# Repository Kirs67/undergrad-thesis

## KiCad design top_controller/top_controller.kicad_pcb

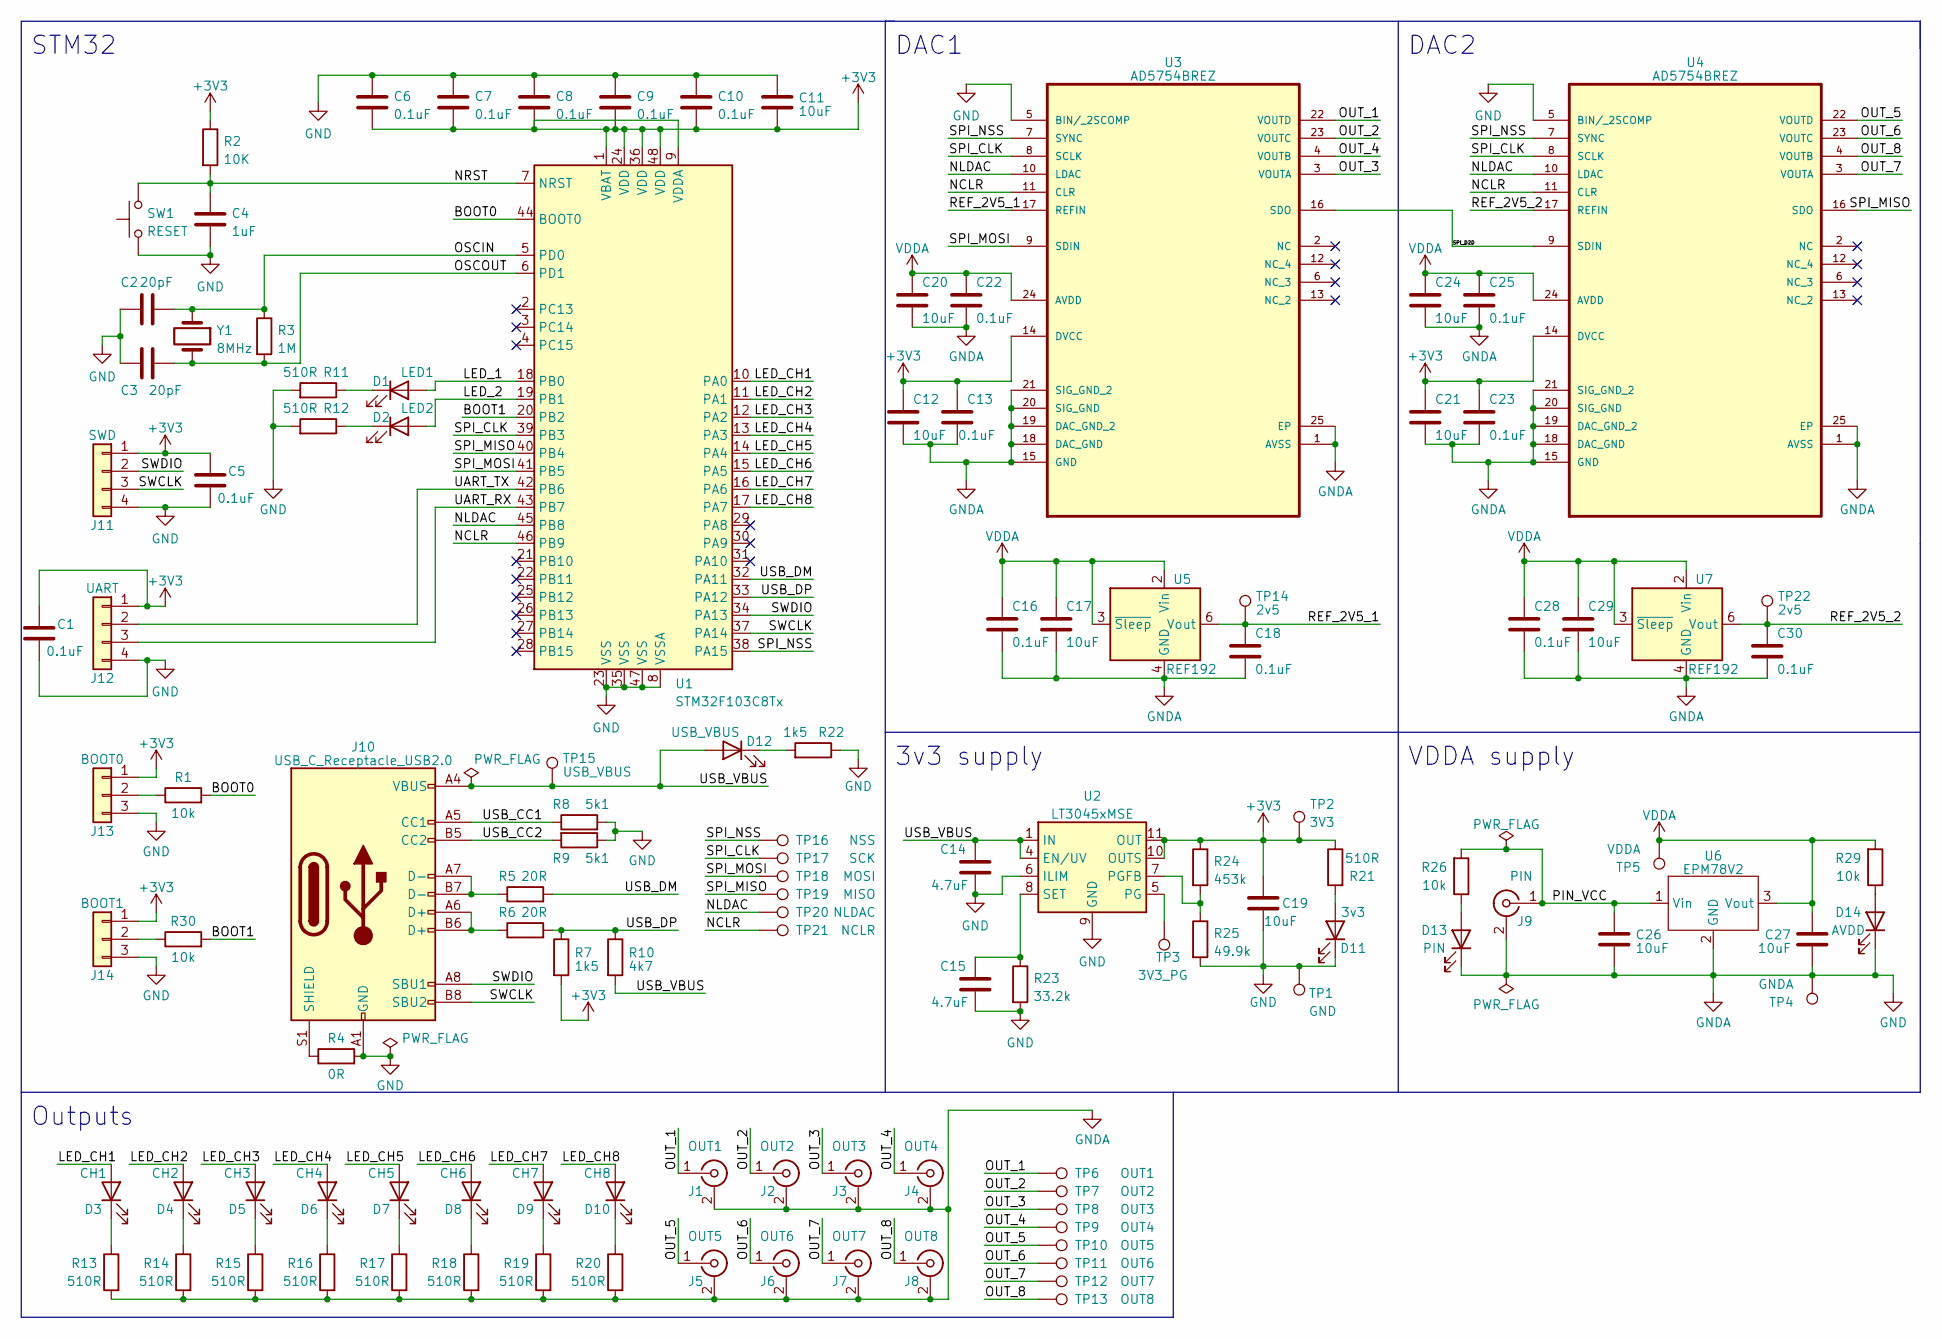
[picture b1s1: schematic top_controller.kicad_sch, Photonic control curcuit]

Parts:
C1, C5, C6, C7, C8, C9, C10, C13, C16, C18, C22, C23, C25, C28, C30: 0.1uF; C_0603_1608Metric
C2, C3: 20pF; C_0603_1608Metric
C4: 1uF; C_0603_1608Metric
C11, C12, C17, C19, C20, C21, C24, C26, C27, C29: 10uF; C_1206_3216Metric
C14, C15: 4.7uF; C_1206_3216Metric
D1: LED1; LED_0805_2012Metric
D2: LED2; LED_0805_2012Metric
D3: CH1; LED_0805_2012Metric
D4: CH2; LED_0805_2012Metric
D5: CH3; LED_0805_2012Metric
D6: CH4; LED_0805_2012Metric
D7: CH5; LED_0805_2012Metric
D8: CH6; LED_0805_2012Metric
D9: CH7; LED_0805_2012Metric
D10: CH8; LED_0805_2012Metric
D11: 3v3; LED_0805_2012Metric
D12: USB_VBUS; LED_0805_2012Metric
D13: PIN; LED_0805_2012Metric
D14: AVDD; LED_0805_2012Metric
J1: OUT1; CONBNC002
J2: OUT2; CONBNC002
J3: OUT3; CONBNC002
J4: OUT4; CONBNC002
J5: OUT5; CONBNC002
J6: OUT6; CONBNC002
J7: OUT7; CONBNC002
J8: OUT8; CONBNC002
J9: PIN; CONBNC002
J10: USB_C_Receptacle_USB2.0; USB_C_Receptacle_GCT_USB4105-xx-A_16P_TopMnt_Horizontal
J11: SWD; PinHeader_1x04_P2.54mm_Vertical
J12: UART; PinHeader_1x04_P2.54mm_Vertical
J13: BOOT0; PinHeader_1x03_P2.54mm_Vertical
J14: BOOT1; PinHeader_1x03_P2.54mm_Vertical
R1, R26, R29, R30: 10k; R_0603_1608Metric
R2: 10K; R_0603_1608Metric
R3: 1M; R_2512_6332Metric
R4: 0R; R_0603_1608Metric
R5, R6: 20R; R_0603_1608Metric
R7, R22: 1k5; R_0603_1608Metric
R8, R9: 5k1; R_0603_1608Metric
R10: 4k7; R_0603_1608Metric
R11, R12, R13, R14, R15, R16, R17, R18, R19, R20, R21: 510R; R_0603_1608Metric
R23: 33.2k; R_0603_1608Metric
R24: 453k; R_0805_2012Metric
R25: 49.9k; R_0603_1608Metric
SW1: RESET; SW_TS04-66-95-BK-100-SMT
TP1: GND; TestPoint_Keystone_5010-5014_Multipurpose
TP2: 3V3; TestPoint_Keystone_5010-5014_Multipurpose
TP3: 3V3_PG; TestPoint_Keystone_5010-5014_Multipurpose
TP4: GNDA; TestPoint_Keystone_5010-5014_Multipurpose
TP5: VDDA; TestPoint_Keystone_5010-5014_Multipurpose
TP6: OUT1; TestPoint_Keystone_5010-5014_Multipurpose
TP7: OUT2; TestPoint_Keystone_5010-5014_Multipurpose
TP8: OUT3; TestPoint_Keystone_5010-5014_Multipurpose
TP9: OUT4; TestPoint_Keystone_5010-5014_Multipurpose
TP10: OUT5; TestPoint_Keystone_5010-5014_Multipurpose
TP11: OUT6; TestPoint_Keystone_5010-5014_Multipurpose
TP12: OUT7; TestPoint_Keystone_5010-5014_Multipurpose
TP13: OUT8; TestPoint_Keystone_5010-5014_Multipurpose
TP14, TP22: 2v5; TestPoint_Keystone_5010-5014_Multipurpose
TP15: USB_VBUS; TestPoint_Keystone_5010-5014_Multipurpose
TP16: NSS; TestPoint_Keystone_5010-5014_Multipurpose
TP17: SCK; TestPoint_Keystone_5010-5014_Multipurpose
TP18: MOSI; TestPoint_Keystone_5010-5014_Multipurpose
TP19: MISO; TestPoint_Keystone_5010-5014_Multipurpose
TP20: NLDAC; TestPoint_Keystone_5010-5014_Multipurpose
TP21: NCLR; TestPoint_Keystone_5010-5014_Multipurpose
U1: STM32F103C8Tx; LQFP-48_7x7mm_P0.5mm
U2: LT3045xMSE; MSOP-12-1EP_3x4mm_P0.65mm_EP1.65x2.85mm
U3, U4: AD5754BREZ; SOP65P640X120-25N; MPN AD5754BREZ
U5, U7: REF192; SOIC-8_3.9x4.9mm_P1.27mm
U6: EPM78V2
Y1: 8MHz; Crystal_SMD_HC49-SD

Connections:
+3V3: C1.1, C5.1, C6.2, C7.2, C8.2, C9.2, C10.2, C11.2, C12.1, C13.1, C19.1, C21.1, C23.1, J11.1, J12.1, J13.1, J14.1, R2.1, R7.2, R21.1, R24.1, TP2.1, U1.1 (VBAT), U1.9 (VDDA), U1.24 (VDD), U1.36 (VDD), U1.48 (VDD), U2.10 (OUTS), U2.11 (OUT), U2.12 (OUT), U3.14 (DVCC), U4.14 (DVCC)
/BOOT0: R1.2, U1.44 (BOOT0)
/BOOT1: R30.2, U1.20 (PB2)
/LED_1: D1.2 (A), U1.18 (PB0)
/LED_2: D2.2 (A), U1.19 (PB1)
/LED_CH1: D3.2 (A), U1.10 (PA0)
/LED_CH2: D4.2 (A), U1.11 (PA1)
/LED_CH3: D5.2 (A), U1.12 (PA2)
/LED_CH4: D6.2 (A), U1.13 (PA3)
/LED_CH5: D7.2 (A), U1.14 (PA4)
/LED_CH6: D8.2 (A), U1.15 (PA5)
/LED_CH7: D9.2 (A), U1.16 (PA6)
/LED_CH8: D10.2 (A), U1.17 (PA7)
/NCLR: TP21.1, U1.46 (PB9), U3.11 (CLR), U4.11 (CLR)
/NLDAC: TP20.1, U1.45 (PB8), U3.10 (LDAC), U4.10 (LDAC)
/NRST: C4.1, R2.2, SW1.2, U1.7 (NRST)
/OSCIN: C2.1, R3.1, U1.5 (PD0), Y1.1
/OSCOUT: C3.1, R3.2, U1.6 (PD1), Y1.2
/OUT_1: J1.1 (In), TP6.1, U3.22 (VOUTD)
/OUT_2: J2.1 (In), TP7.1, U3.23 (VOUTC)
/OUT_3: J3.1 (In), TP8.1, U3.3 (VOUTA)
/OUT_4: J4.1 (In), TP9.1, U3.4 (VOUTB)
/OUT_5: J5.1 (In), TP10.1, U4.22 (VOUTD)
/OUT_6: J6.1 (In), TP11.1, U4.23 (VOUTC)
/OUT_7: J7.1 (In), TP12.1, U4.3 (VOUTA)
/OUT_8: J8.1 (In), TP13.1, U4.4 (VOUTB)
/PIN_VCC: C26.1, J9.1 (In), R26.2, U6.1 (Vin)
/REF_2V5_1: C18.1, TP14.1, U3.17 (REFIN), U5.6 (Vout)
/REF_2V5_2: C30.1, TP22.1, U4.17 (REFIN), U7.6 (Vout)
/SPI_CLK: TP17.1, U1.39 (PB3), U3.8 (SCLK), U4.8 (SCLK)
/SPI_D2D: U3.16 (SDO), U4.9 (SDIN)
/SPI_MISO: TP19.1, U1.40 (PB4), U4.16 (SDO)
/SPI_MOSI: TP18.1, U1.41 (PB5), U3.9 (SDIN)
/SPI_NSS: TP16.1, U1.38 (PA15), U3.7 (SYNC), U4.7 (SYNC)
/SWCLK: J10.B8 (SBU2), J11.3, U1.37 (PA14)
/SWDIO: J10.A8 (SBU1), J11.2, U1.34 (PA13)
/UART_RX: J12.3, U1.43 (PB7)
/UART_TX: J12.2, U1.42 (PB6)
/USB_CC1: J10.A5 (CC1), R8.1
/USB_CC2: J10.B5 (CC2), R9.2
/USB_DM: R5.2, U1.32 (PA11)
/USB_DP: R6.2, R7.1, R10.1, U1.33 (PA12)
/USB_VBUS: C14.1, D12.2 (A), J10.A4 (VBUS), J10.A9 (VBUS), J10.B4 (VBUS), J10.B9 (VBUS), R10.2, TP15.1, U2.1 (IN), U2.2 (IN), U2.3 (IN), U2.4 (EN/UV)
GND: C1.2, C2.2, C3.2, C4.2, C5.2, C6.1, C7.1, C8.1, C9.1, C10.1, C11.1, C12.2, C13.2, C14.2, C15.2, C16.2, C17.2, C18.2, C19.2, C20.2, C21.2, C22.2, C23.2, C24.2, C25.2, C26.2, C27.2, C28.2, C29.2, C30.2, D11.1 (K), D13.1 (K), D14.1 (K), J1.2 (Ext), J2.2 (Ext), J3.2 (Ext), J4.2 (Ext), J5.2 (Ext), J6.2 (Ext), J7.2 (Ext), J8.2 (Ext), J9.2 (Ext), J10.A1 (GND), J10.A12 (GND), J10.B1 (GND), J10.B12 (GND), J11.4, J12.4, J13.3, J14.3, R4.2, R8.2, R9.1, R11.2, R12.2, R13.2, R14.2, R15.2, R16.2, R17.2, R18.2, R19.2, R20.2, R22.1, R23.2, R25.2, SW1.1, TP1.1, TP4.1, U1.8 (VSSA), U1.23 (VSS), U1.35 (VSS), U1.47 (VSS), U2.6 (ILIM), U2.9 (GND), U2.13 (GND), U3.1 (AVSS), U3.5 (BIN/_2SCOMP), U3.15 (GND), U3.18 (DAC_GND), U3.19 (DAC_GND_2), U3.20 (SIG_GND), U3.21 (SIG_GND_2), U3.25 (EP), U4.1 (AVSS), U4.5 (BIN/_2SCOMP), U4.15 (GND), U4.18 (DAC_GND), U4.19 (DAC_GND_2), U4.20 (SIG_GND), U4.21 (SIG_GND_2), U4.25 (EP), U5.4 (GND), U6.2 (GND), U7.4 (GND)
unnamed: D1.1 (K), R11.1
unnamed: D2.1 (K), R12.1
unnamed: D3.1 (K), R13.1
unnamed: D4.1 (K), R14.1
unnamed: D5.1 (K), R15.1
unnamed: D6.1 (K), R16.1
unnamed: D7.1 (K), R17.1
unnamed: D8.1 (K), R18.1
unnamed: D9.1 (K), R19.1
unnamed: D10.1 (K), R20.1
unnamed: D11.2 (A), R21.2
unnamed: D12.1 (K), R22.2
unnamed: D13.2 (A), R26.1
unnamed: D14.2 (A), R29.1
unnamed: J10.A6 (D+), J10.B6 (D+), R6.1
unnamed: J10.A7 (D-), J10.B7 (D-), R5.1
unnamed: J10.S1 (SHIELD), R4.1
unnamed: J13.2, R1.1
unnamed: J14.2, R30.1
unnamed: TP3.1, U2.5 (PG)
unnamed: R24.2, R25.1, U2.7 (PGFB)
unnamed: C15.1, R23.1, U2.8 (SET)
VDDA: C16.1, C17.1, C20.1, C22.1, C24.1, C25.1, C27.1, C28.1, C29.1, R29.2, TP5.1, U3.24 (AVDD), U4.24 (AVDD), U5.2 (Vin), U5.3 (~Sleep), U6.3 (Vout), U7.2 (Vin), U7.3 (~Sleep)

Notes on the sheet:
DAC2
3v3 supply
Outputs
DAC1
VDDA supply
STM32

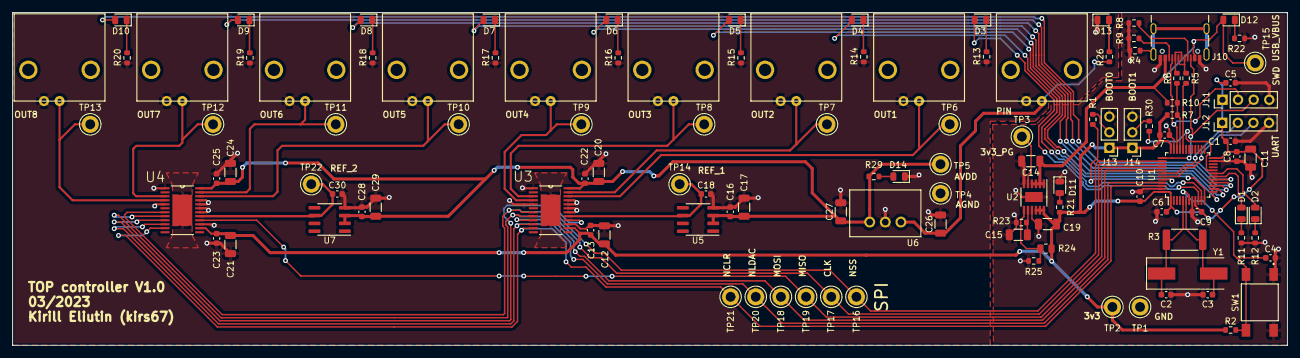
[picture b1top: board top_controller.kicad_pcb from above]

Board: 2 copper layers, 207.7 x 54.2 mm, 117 parts (0 on the bottom side), 67 nets.

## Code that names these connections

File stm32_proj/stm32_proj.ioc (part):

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Mcu.Name=STM32F103C(8-B)Tx
Mcu.Package=LQFP48
Mcu.UserName=STM32F103C8Tx
PA0-WKUP.GPIOParameters=GPIO_Label
PA0-WKUP.GPIO_Label=LED_CH1
PA0-WKUP.Signal=GPIO_Output
PA1.GPIOParameters=GPIO_Label
PA1.GPIO_Label=LED_CH2
PA1.Signal=GPIO_Output
PA11.Mode=Device
PA11.Signal=USB_DM
PA12.Mode=Device
PA12.Signal=USB_DP
PA13.Mode=Serial_Wire
PA13.Signal=SYS_JTMS-SWDIO
PA14.Mode=Serial_Wire
PA14.Signal=SYS_JTCK-SWCLK
PA15.Mode=NSS_Signal_Hard_Output
PA15.Signal=SPI1_NSS
PA2.GPIOParameters=GPIO_Label
PA2.GPIO_Label=LED_CH3
PA2.Signal=GPIO_Output
PA3.GPIOParameters=GPIO_Label
PA3.GPIO_Label=LED_CH4
PA3.Signal=GPIO_Output
PA4.GPIOParameters=GPIO_Label
PA4.GPIO_Label=LED_CH5
PA4.Signal=GPIO_Output
PA5.GPIOParameters=GPIO_Label
PA5.GPIO_Label=LED_CH6
PA5.Signal=GPIO_Output
PA6.GPIOParameters=GPIO_Label
PA6.GPIO_Label=LED_CH7
PA6.Signal=GPIO_Output
PA7.GPIOParameters=GPIO_Label
PA7.GPIO_Label=LED_CH8
PA7.Signal=GPIO_Output
PB0.GPIOParameters=GPIO_Label
PB0.GPIO_Label=LED1
PB0.Signal=GPIO_Output
PB1.GPIOParameters=GPIO_Label
PB1.GPIO_Label=LED2
PB1.Signal=GPIO_Output
PB2.GPIOParameters=GPIO_Label
PB2.GPIO_Label=BOOT1
PB2.Signal=GPIO_Input
PB3.Mode=Full_Duplex_Master
PB3.Signal=SPI1_SCK
PB4.Mode=Full_Duplex_Master
PB4.Signal=SPI1_MISO
PB5.Mode=Full_Duplex_Master
PB5.Signal=SPI1_MOSI
PB6.Mode=Asynchronous
PB6.Signal=USART1_TX
PB7.Mode=Asynchronous
PB7.Signal=USART1_RX
PB8.GPIOParameters=GPIO_Label
PB8.GPIO_Label=NLDAC
PB8.Signal=GPIO_Output
PB9.GPIOParameters=GPIO_Label
PB9.GPIO_Label=NCLR
PB9.Signal=GPIO_Output
PD0-OSC_IN.Mode=HSE-External-Oscillator
PD0-OSC_IN.Signal=RCC_OSC_IN
PD1-OSC_OUT.Mode=HSE-External-Oscillator
PD1-OSC_OUT.Signal=RCC_OSC_OUT
RCC.SYSCLKFreq_VALUE=48000000
RCC.SYSCLKSource=RCC_SYSCLKSOURCE_PLLCLK
board=custom

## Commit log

2023-03-12 Most of the schematic done
2023-03-20 schematic is finished (except LEDs)
2023-03-20 Finalized the schematic Added LEDs and UART
2023-03-20 Added gitignore and deleted backups/temp files from the repo
2023-03-21 Small fixes - Power supplied to VBAT of STM32 - Added 10uF cap for the whole STM32 - Added BOOT0 switch - Labelled some unlabelled nets - Added resistor between USB connector SHIELD and GND - Marked 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
2023-03-21 Assigned footprints
2023-03-21 Added testpoints
2023-03-22 Added BOOT1
2023-03-24 Part of the board is done
2023-03-24 Added cubemx project
2023-03-26 Added second voltage reference
2023-03-26 GNDA and VDDA redone properly, slightly changed component placement in the schematic
2023-03-26 Restructured schematic again - LEDs moved to better locations
2023-03-26 Added capacitors around DC-DC regulator
2023-03-26 Changed STM LED pins to more convenient ones
2023-03-26 Changed data pins on STM32 for easier tracing
2023-03-26 Placed all the components
2023-03-26 Reordered output channels on DACs for easier tracing
2023-03-27 Most of the signals routed
2023-03-27 Finished all the traces (except connecting two grounds and testpoints on SPI)
2023-03-27 Finished tracing - still some errors present
2023-03-27 Fixed a bunch of DRC errors - Fixed couple place where 3v3 was not routed - Allowed for 1 connection between pad and thermal relief (cause kicad counts just connectin a pad to the ground plane as the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
2023-03-27 Increased silkscreen thickness from 0.15 to 0.153
2023-03-27 Fixed most of the silk issues (except BNC connectors having outline too close to the edge)
2023-03-27 Cut Type C connector pands to meet the constraints
2023-03-27 DRC errors solved
2023-03-27 Made power traces wider
2023-03-27 Increased output traces width
2023-03-27 Added labels on silkscreen
2023-03-27 Generated Gerber and drill files
2023-03-28 Added a place for JLCPCB order number
